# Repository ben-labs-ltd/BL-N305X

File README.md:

# BL-N305X
Meshtastic intended LoRa Node - Ben Labs Node 30.5dBm

## BL-N305A

Prototype board

## BL-N305B

Production ready board

OEM Price Point target £50
DIY Price Point target £30

### Considerations
- Use the SKY66122
- Move to using a bias-tee module for the amplification
- Compact compact compact

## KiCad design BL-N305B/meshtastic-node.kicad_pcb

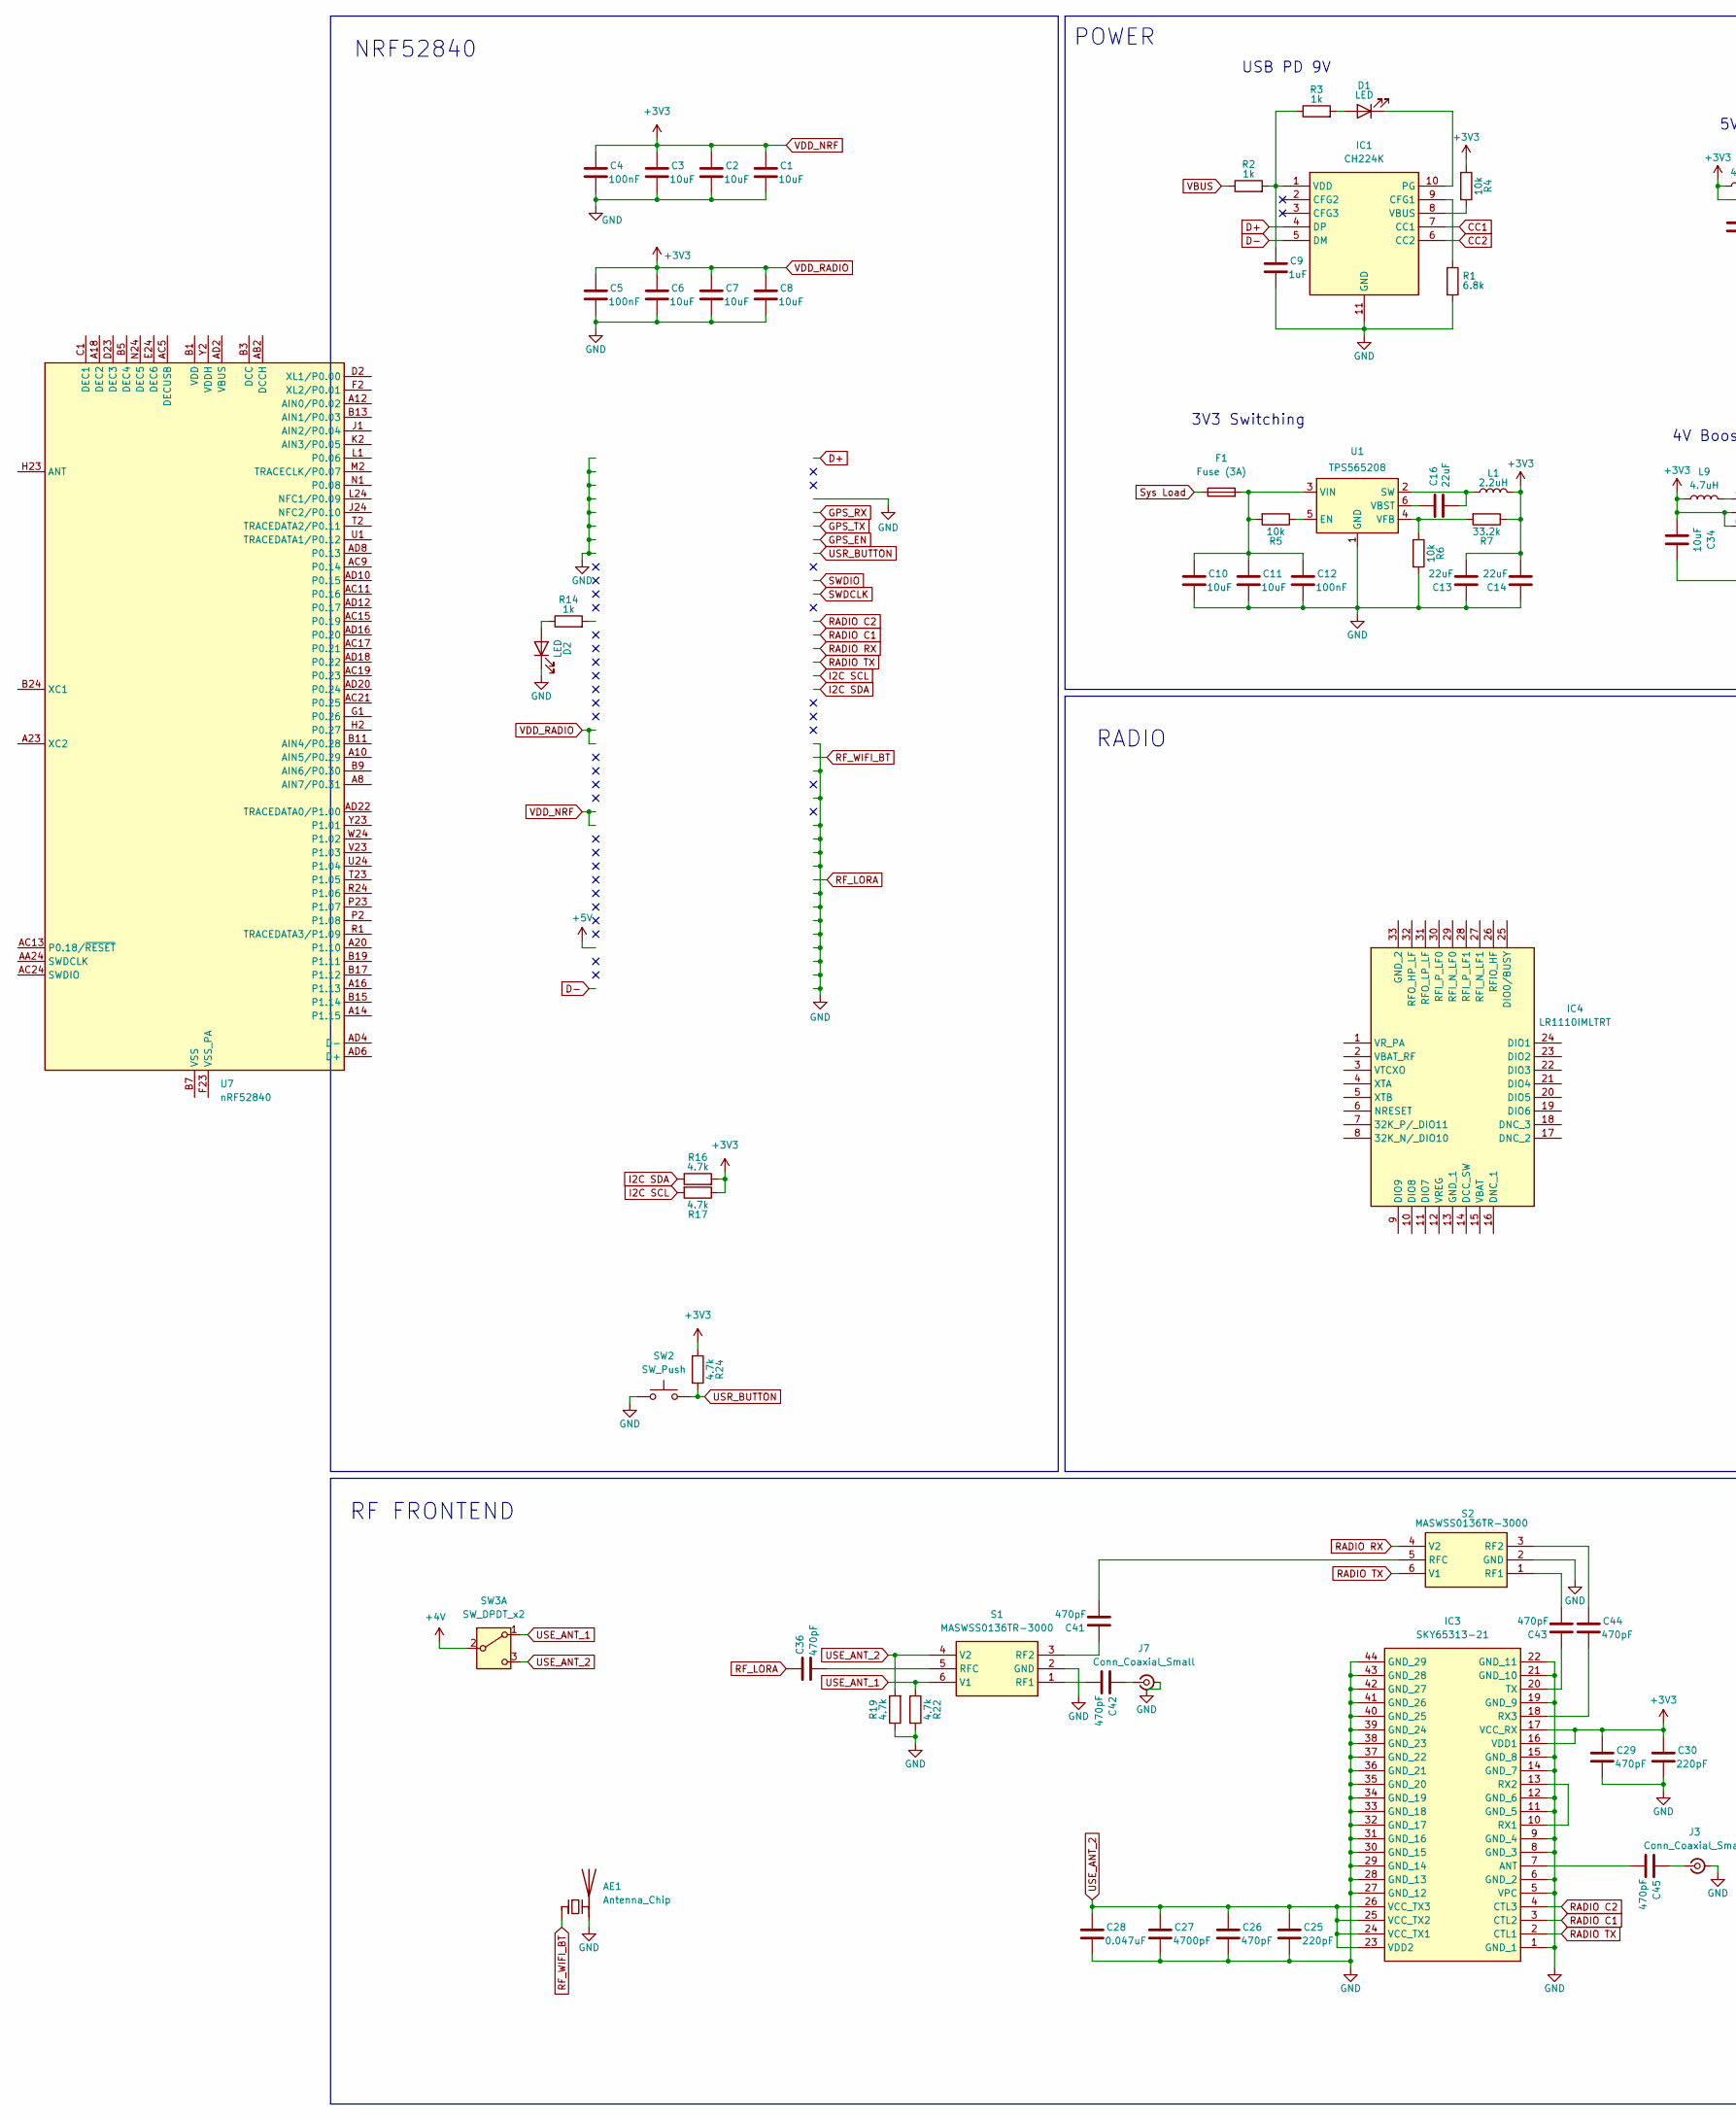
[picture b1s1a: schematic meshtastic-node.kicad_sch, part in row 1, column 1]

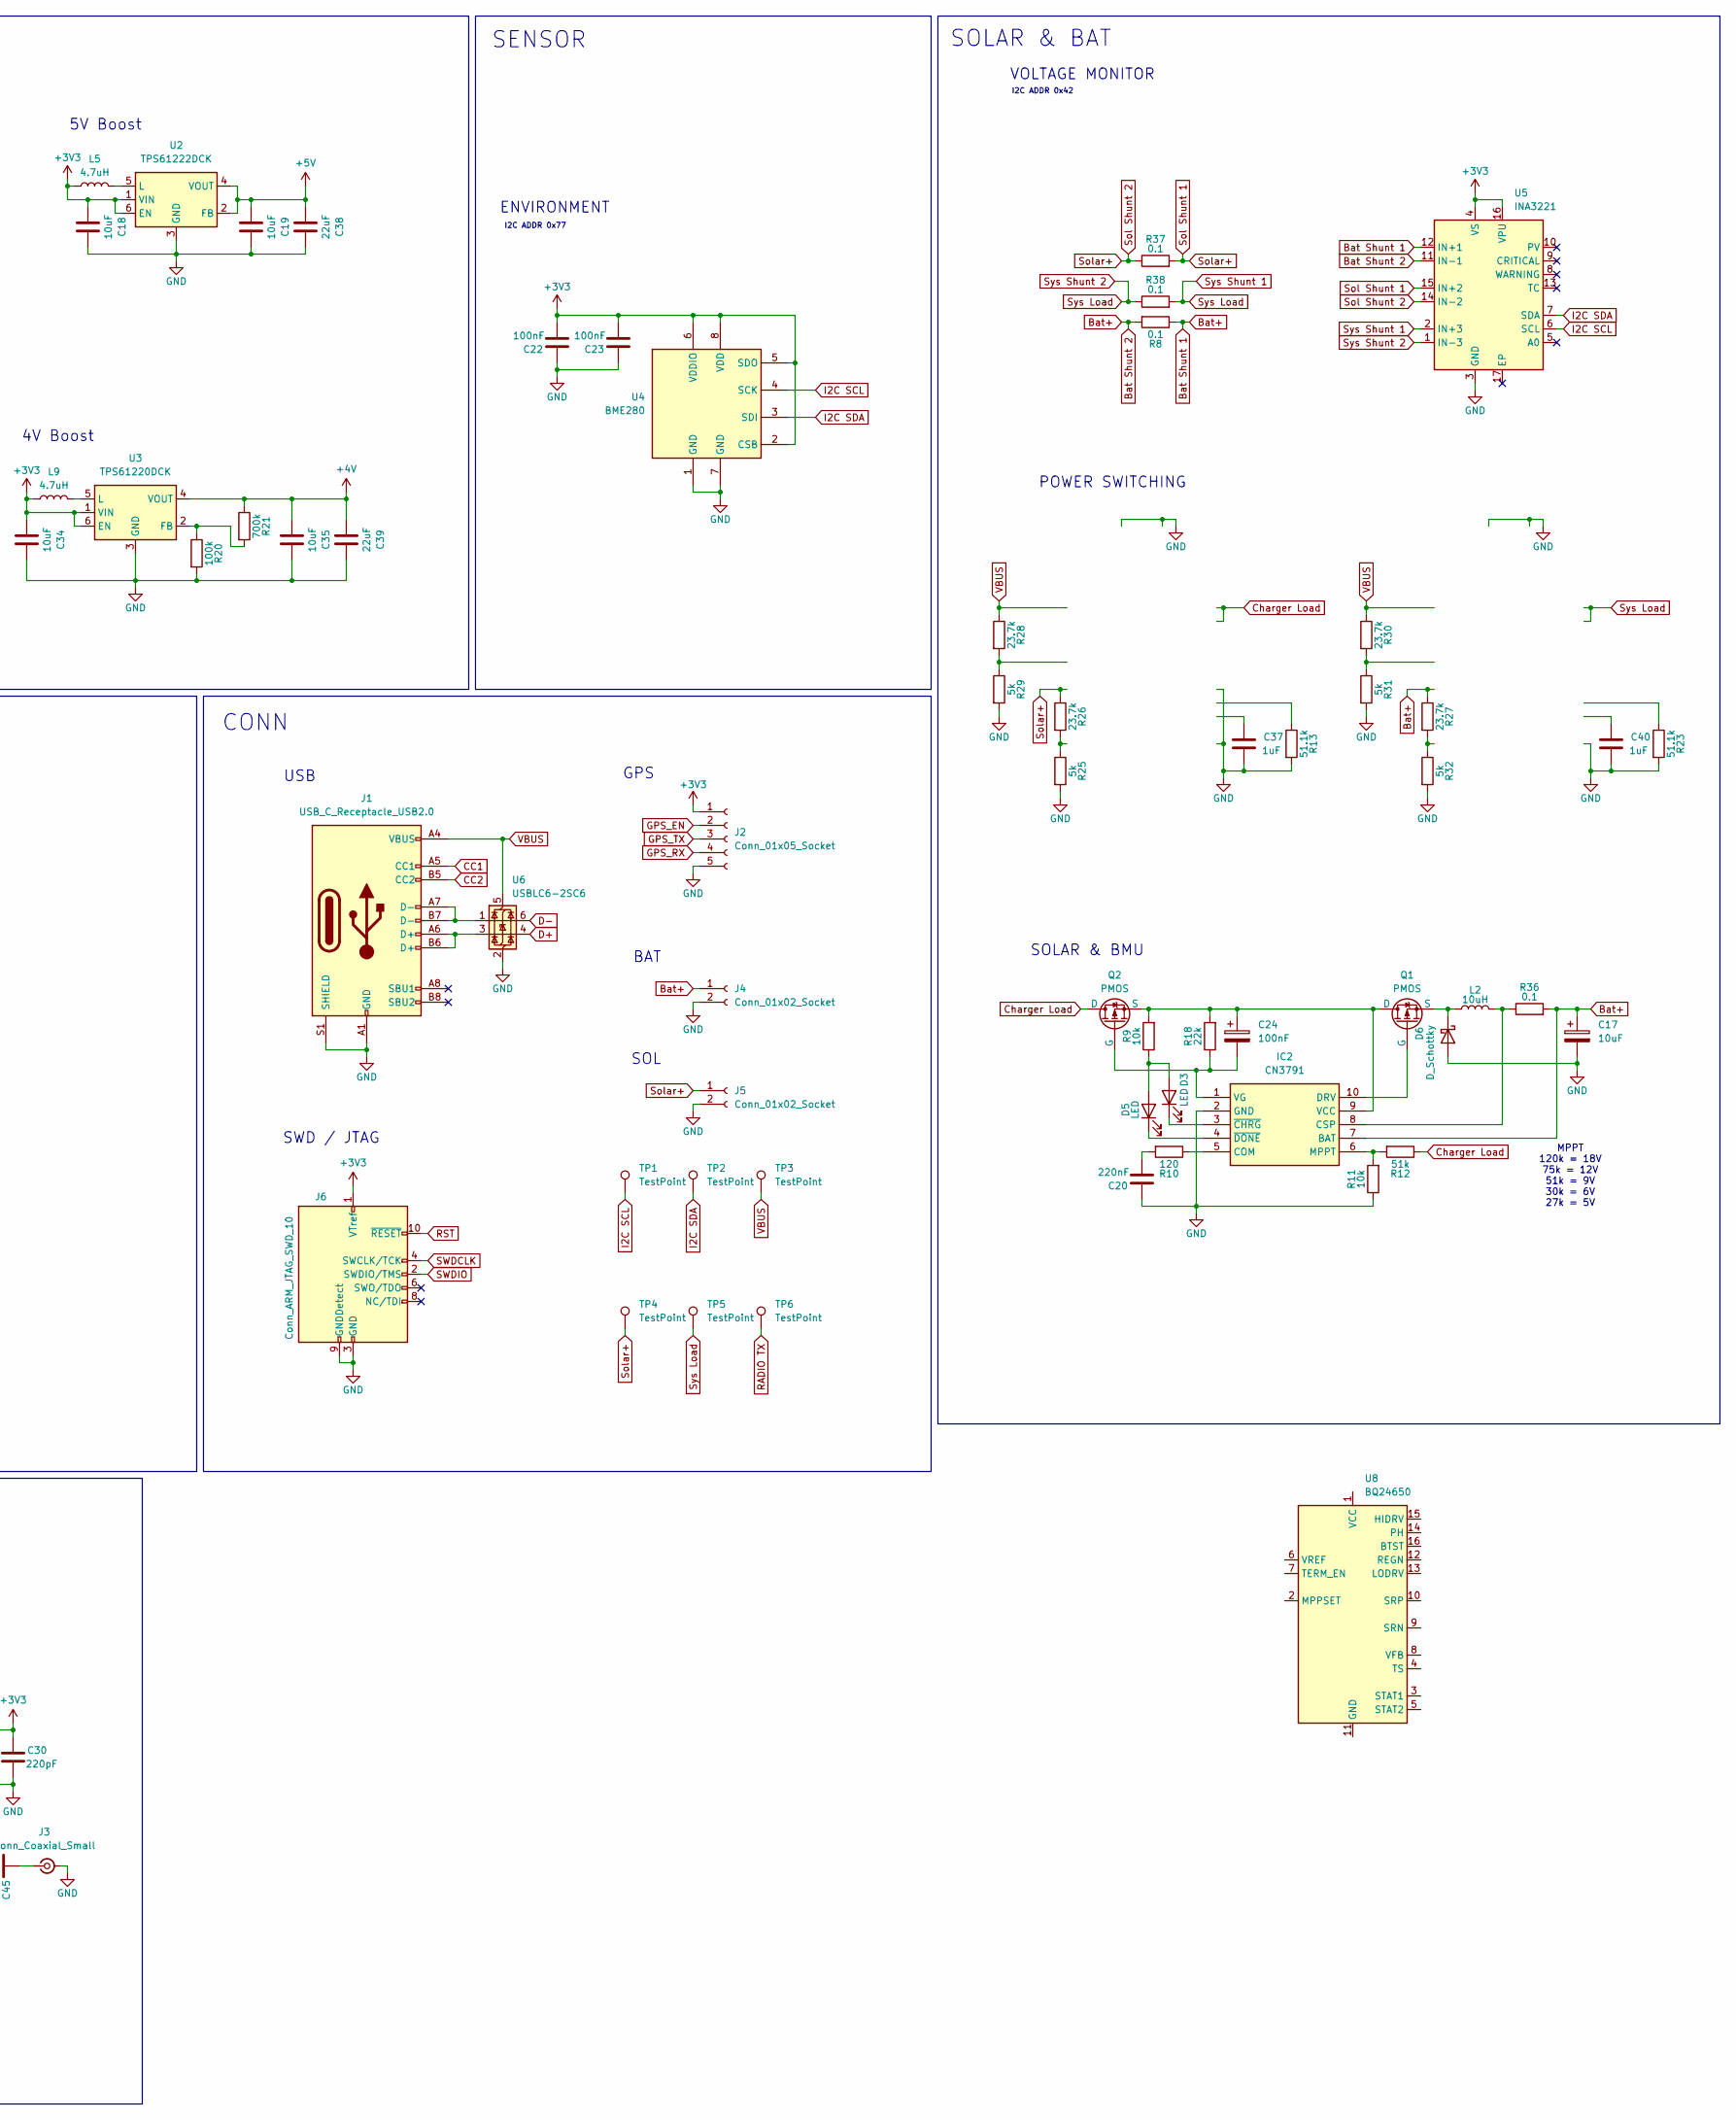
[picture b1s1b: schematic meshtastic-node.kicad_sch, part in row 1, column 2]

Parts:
AE1: Antenna_Chip; Texas_SWRA117D_2.4GHz_Left
C1, C2, C3, C6, C7, C8, C10, C11, C18, C19, C34, C35: 10uF; C_0805_2012Metric_Pad1.18x1.45mm_HandSolder
C4, C5, C12, C22, C23: 100nF; C_0805_2012Metric_Pad1.18x1.45mm_HandSolder
C9, C37, C40: 1uF; C_0805_2012Metric_Pad1.18x1.45mm_HandSolder
C13, C14, C16, C38, C39: 22uF; C_0805_2012Metric_Pad1.18x1.45mm_HandSolder
C17: 10uF; CP_Elec_4x5.4
C20: 220nF; C_0805_2012Metric_Pad1.18x1.45mm_HandSolder
C24: 100nF; CP_Elec_4x5.4
C25, C30: 220pF; C_0603_1608Metric_Pad1.08x0.95mm_HandSolder
C26, C29, C36, C41, C42, C43, C44, C45: 470pF; C_0603_1608Metric_Pad1.08x0.95mm_HandSolder
C27: 4700pF; C_0603_1608Metric_Pad1.08x0.95mm_HandSolder
C28: 0.047uF; C_0603_1608Metric_Pad1.08x0.95mm_HandSolder
D1, D2, D3, D5: LED; LED_0805_2012Metric_Pad1.15x1.40mm_HandSolder
D6: D_Schottky; D_SOD-123
F1: Fuse (3A); Fuse_0603_1608Metric_Pad1.05x0.95mm_HandSolder
IC1: CH224K; SOP100P600X180-11N; Manufacturer_Part_Number CH224K; LCSC C970725
IC2: CN3791; SOP100P600X175-10N; Manufacturer_Part_Number CN3791; LCSC C154992
IC3: SKY65313-21; SKY6531321; Manufacturer_Part_Number SKY65313-21; Mouser Part Number 873-SKY65313-21
IC4: LR1110IMLTRT; QFN50P500X500X100-33N-D; Manufacturer_Part_Number LR1110IMLTRT; Mouser Part Number 947-LR1110IMLTRT
J1: USB_C_Receptacle_USB2.0; USB_C_Receptacle_G-Switch_GT-USB-7010ASV
J2: Conn_01x05_Socket; JST_EH_S5B-EH_1x05_P2.50mm_Horizontal
J3, J7: Conn_Coaxial_Small; SMA_Molex_73251-1153_EdgeMount_Horizontal
J4, J5: Conn_01x02_Socket; JST_EH_S2B-EH_1x02_P2.50mm_Horizontal
J6: Conn_ARM_JTAG_SWD_10; PinHeader_2x05_P1.27mm_Vertical
L1: 2.2uH; L_SXN_SMDRI124; LCSC C2929497
L2: 10uH; L_0805_2012Metric_Pad1.15x1.40mm_HandSolder
L5, L9: 4.7uH; L_0805_2012Metric_Pad1.15x1.40mm_HandSolder
Q1, Q2: PMOS; SOT-23_Handsoldering
R1: 6.8k; R_0805_2012Metric_Pad1.20x1.40mm_HandSolder
R2, R3, R14: 1k; R_0805_2012Metric_Pad1.20x1.40mm_HandSolder
R4, R5, R6, R9, R11: 10k; R_0805_2012Metric_Pad1.20x1.40mm_HandSolder
R7: 33.2k; R_0805_2012Metric_Pad1.20x1.40mm_HandSolder
R8, R36, R37, R38: 0.1; R_2512_6332Metric_Pad1.40x3.35mm_HandSolder
R10: 120; R_0805_2012Metric_Pad1.20x1.40mm_HandSolder
R12: 51k; R_0805_2012Metric_Pad1.20x1.40mm_HandSolder
R13, R23: 51.1k; R_0805_2012Metric_Pad1.20x1.40mm_HandSolder
R16, R17, R19, R22, R24: 4.7k; R_0805_2012Metric_Pad1.20x1.40mm_HandSolder
R18: 22k; R_0805_2012Metric_Pad1.20x1.40mm_HandSolder
R20: 100k; R_0805_2012Metric_Pad1.20x1.40mm_HandSolder
R21: 700k; R_0805_2012Metric_Pad1.20x1.40mm_HandSolder
R25, R29, R31, R32: 5k; R_0805_2012Metric_Pad1.20x1.40mm_HandSolder
R26, R27, R28, R30: 23.7k; R_0805_2012Metric_Pad1.20x1.40mm_HandSolder
S1, S2: MASWSS0136TR-3000; SOT65P210X110-6N; Manufacturer_Part_Number MASWSS0136TR-3000; Mouser Part Number 937-MASWSS0136-T
SW2: SW_Push; SW_Push_1P1T_XKB_TS-1187A; LCSC C42420254
SW3: SW_DPDT_x2; SS3235SL3; LCSC C381098
TP1, TP2, TP3, TP4, TP5, TP6: TestPoint; TestPoint_Pad_D2.0mm
U1: TPS565208; SOT-23-6; LCSC C2650336
U2: TPS61222DCK; Texas_R-PDSO-G6; LCSC C116461
U3: TPS61220DCK; Texas_R-PDSO-G6; LCSC C116461
U4: BME280; Bosch_LGA-8_2.5x2.5mm_P0.65mm_ClockwisePinNumbering; LCSC C92489
U5: INA3221; Texas_RGV0016A_VQFN-16-1EP_4x4mm_P0.65mm_EP2.1x2.1mm; LCSC C181255
U6: USBLC6-2SC6; SOT-23-6
U7: nRF52840; Nordic_AQFN-73-1EP_7x7mm_P0.5mm
U8: BQ24650; Texas_RVA_VQFN-16-1EP_3.5x3.5mm_P0.5mm_EP2.14x2.14mm_Therma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

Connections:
+4V: C35.1, C39.1, R21.1, SW3.2 (B), U3.4 (VOUT)
+5V: C19.1, C38.1, U2.2 (FB), U2.4 (VOUT)
Bat Shunt 1: C17.1, IC2.7 (BAT), J4.1, R8.1, R8.2, R27.1, R36.2, U5.11 (IN-1), U5.12 (IN+1)
CC1: IC1.7 (CC1), J1.A5 (CC1)
CC2: IC1.6 (CC2), J1.B5 (CC2)
Charger Load: Q2.1 (D), R12.1
D+: IC1.4 (DP), U6.4 (I/O2)
D-: IC1.5 (DM), U6.6 (I/O1)
GND: AE1.2 (PCB_Trace), C1.2, C2.2, C3.2, C4.2, C5.2, C6.2, C7.2, C8.2, C9.2, C10.2, C11.2, C12.2, C13.1, C14.1, C17.2, C18.2, C19.2, C20.1, C22.1, C23.1, C25.2, C26.2, C27.2, C28.2, C29.2, C30.2, C34.2, C35.2, C37.2, C38.2, C39.2, C40.2, D2.1 (K), D6.2 (A), IC1.11 (GND), IC2.2 (GND), IC3.1 (GND_1), IC3.5 (VPC), IC3.6 (GND_2), IC3.8 (GND_3), IC3.9 (GND_4), IC3.11 (GND_5), IC3.12 (GND_6), IC3.14 (GND_7), IC3.15 (GND_8), IC3.19 (GND_9), IC3.21 (GND_10), IC3.22 (GND_11), IC3.27 (GND_12), IC3.28 (GND_13), IC3.29 (GND_14), IC3.30 (GND_15), IC3.31 (GND_16), IC3.32 (GND_17), IC3.33 (GND_18), IC3.34 (GND_19), IC3.35 (GND_20), IC3.36 (GND_21), IC3.37 (GND_22), IC3.38 (GND_23), IC3.39 (GND_24), IC3.40 (GND_25), IC3.41 (GND_26), IC3.42 (GND_27), IC3.43 (GND_28), IC3.44 (GND_29), J1.A1 (GND), J1.A12 (GND), J1.B1 (GND), J1.B12 (GND), J1.S1 (SHIELD), J2.5, J3.2 (Ext), J4.2, J5.2, J6.3 (GND), J6.5 (GND), J6.9 (GNDDetect), J7.2 (Ext), R1.2, R6.2, R11.1, R13.2, R19.1, R20.2, R22.2, R23.2, R25.2, R29.2, R31.2, R32.2, S1.2 (GND), S2.2 (GND), SW2.1, U1.1 (GND), U2.3 (GND), U3.3 (GND), U4.1 (GND), U4.7 (GND), U5.3 (GND), U6.2 (GND)
GPS_EN: J2.2
GPS_RX: J2.4
GPS_TX: J2.3
I2C SCL: R17.2, TP1.1, U4.4 (SCK), U5.6 (SCL)
I2C SDA: R16.1, TP2.1, U4.3 (SDI), U5.7 (SDA)
unnamed: C20.2, R10.2
unnamed: D1.2 (A), R3.2
unnamed: D1.1 (K), IC1.10 (PG)
unnamed: D2.2 (A), R14.1
unnamed: D3.2 (A), D5.2 (A), R9.1
unnamed: D3.1 (K), IC2.3 (~CHRG)
unnamed: D5.1 (K), IC2.4 (~DONE)
unnamed: D6.1 (K), L2.1, Q1.3 (S)
unnamed: IC1.9 (CFG1), R1.1
unnamed: IC1.8 (VBUS), R4.2
unnamed: C9.1, IC1.1 (VDD), R2.2, R3.1
unnamed: IC2.5 (COM), R10.1
unnamed: IC2.8 (CSP), L2.2, R36.1
unnamed: IC2.10 (DRV), Q1.2 (G)
unnamed: IC2.6 (MPPT), R11.2, R12.2
unnamed: C24.1, IC2.9 (VCC), Q1.1 (D), Q2.3 (S), R9.2, R18.2
unnamed: C24.2, IC2.1 (VG), Q2.2 (G), R18.1
unnamed: C45.2, IC3.7 (ANT)
unnamed: IC3.10 (RX1), IC3.13 (RX2)
unnamed: C44.2, IC3.18 (RX3)
unnamed: C43.1, IC3.20 (TX)
unnamed: J1.A6 (D+), J1.B6 (D+), U6.3 (I/O2)
unnamed: J1.A7 (D-), J1.B7 (D-), U6.1 (I/O1)
unnamed: C45.1, J3.1 (In)
unnamed: C42.1, J7.1 (In)
unnamed: R25.1, R26.2
unnamed: R27.2, R32.1
unnamed: R28.2, R29.1
unnamed: R30.2, R31.1
unnamed: C42.2, S1.1 (RF1)
unnamed: C41.1, S1.3 (RF2)
unnamed: C36.2, S1.5 (RFC)
unnamed: C43.2, S2.1 (RF1)
unnamed: C44.1, S2.3 (RF2)
unnamed: C41.2, S2.5 (RFC)
unnamed: R5.1, U1.5 (EN)
unnamed: C16.2, L1.1, U1.2 (SW)
unnamed: C16.1, U1.6 (VBST)
unnamed: R6.1, R7.2, U1.4 (VFB)
unnamed: C10.1, C11.1, C12.1, F1.2, R5.2, U1.3 (VIN)
unnamed: L5.2, U2.5 (L)
unnamed: R20.1, R21.2, U3.2 (FB)
unnamed: L9.2, U3.5 (L)
unnamed: U7.A22 (VDD), U7.AD14 (VDD), U7.AD23 (VDD), U7.B1 (VDD), U7.W1 (VDD)
unnamed: U7.B7 (VSS), U7.EP (VSS)
unnamed: U8.11 (GND), U8.17 (GND)
RADIO C1: IC3.3 (CTL2)
RADIO C2: IC3.4 (CTL3)
RADIO RX: S2.4 (V2)
RADIO TX: IC3.2 (CTL1), S2.6 (V1), TP6.1
RF_LORA: C36.1
RF_WIFI_BT: AE1.1 (FEED)
RST: J6.10 (~RESET)
SWDCLK: J6.4 (SWCLK/TCK)
SWDIO: J6.2 (SWDIO/TMS)
Sol Shunt 1: J5.1, R26.1, R37.1, R37.2, TP4.1, U5.14 (IN-2), U5.15 (IN+2)
Sys Load: F1.1, R38.1, R38.2, TP5.1, U5.1 (IN-3), U5.2 (IN+3)
USE_ANT_1: R22.1, S1.6 (V1), SW3.1 (A)
USE_ANT_2: C25.1, C26.1, C27.1, C28.1, IC3.23 (VDD2), IC3.24 (VCC_TX1), IC3.25 (VCC_TX2), IC3.26 (VCC_TX3), R19.2, S1.4 (V2), SW3.3 (C)
USR_BUTTON: R24.2, SW2.2
VBUS: J1.A4 (VBUS), J1.A9 (VBUS), J1.B4 (VBUS), J1.B9 (VBUS), R2.1, R28.1, R30.1, TP3.1, U6.5 (VBUS)
VDD_NRF: C1.1, C2.1, C3.1, C4.1, C5.1, C6.1, C7.1, C8.1, C13.2, C14.2, C18.1, C22.2, C23.2, C29.1, C30.1, C34.1, IC3.16 (VDD1), IC3.17 (VCC_RX), J2.1, J6.1 (VTref), L1.2, L5.1, L9.1, R4.1, R7.1, R16.2, R17.1, R24.1, U2.1 (VIN), U2.6 (EN), U3.1 (VIN), U3.6 (EN), U4.2 (CSB), U4.5 (SDO), U4.6 (VDDIO), U4.8 (VDD), U5.4 (VS), U5.16 (VPU)

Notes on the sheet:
I2C ADDR 0x77
3V3 Switching
GPS
MPPT 120k = 18V 75k = 12V 51k = 9V 30k = 6V 27k = 5V
ENVIRONMENT
BAT
SENSOR
RADIO
VOLTAGE MONITOR
5V Boost
CONN
SOL
4V Boost
SOLAR & BAT
SWD / JTAG
I2C ADDR 0x42
NRF52840
USB PD 9V
SOLAR & BMU
POWER
USB
RF FRONTEND
POWER SWITCHING

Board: 2 copper layers, 115 parts (0 on the bottom side), 64 nets, no tracks yet.

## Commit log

2025-04-16 add images
2025-04-25 rev b
2025-05-06 schematic
2025-05-14 networks
